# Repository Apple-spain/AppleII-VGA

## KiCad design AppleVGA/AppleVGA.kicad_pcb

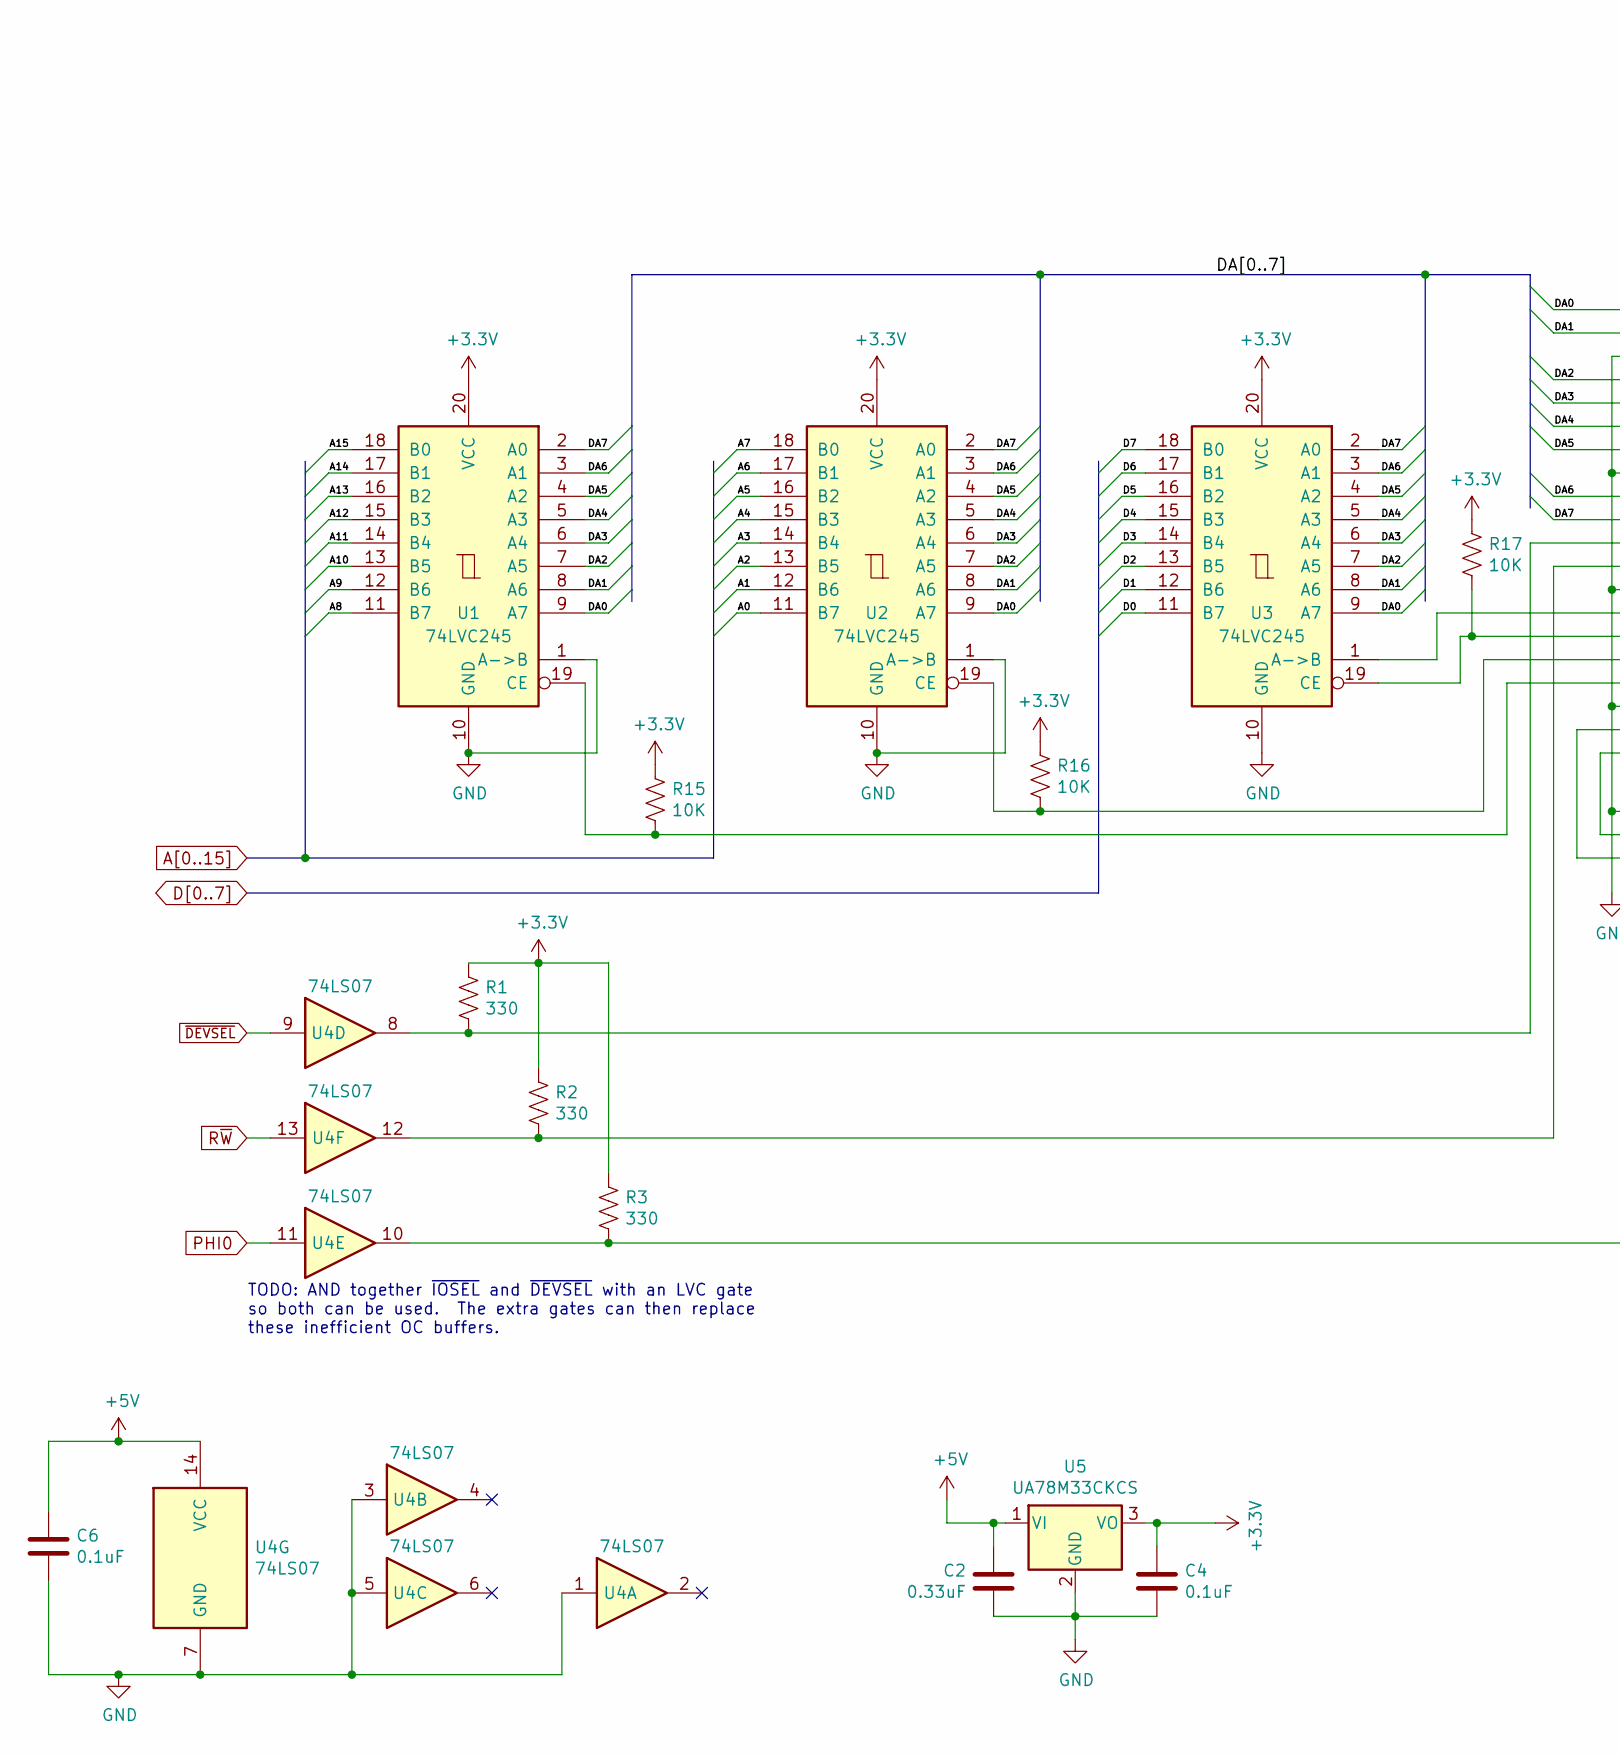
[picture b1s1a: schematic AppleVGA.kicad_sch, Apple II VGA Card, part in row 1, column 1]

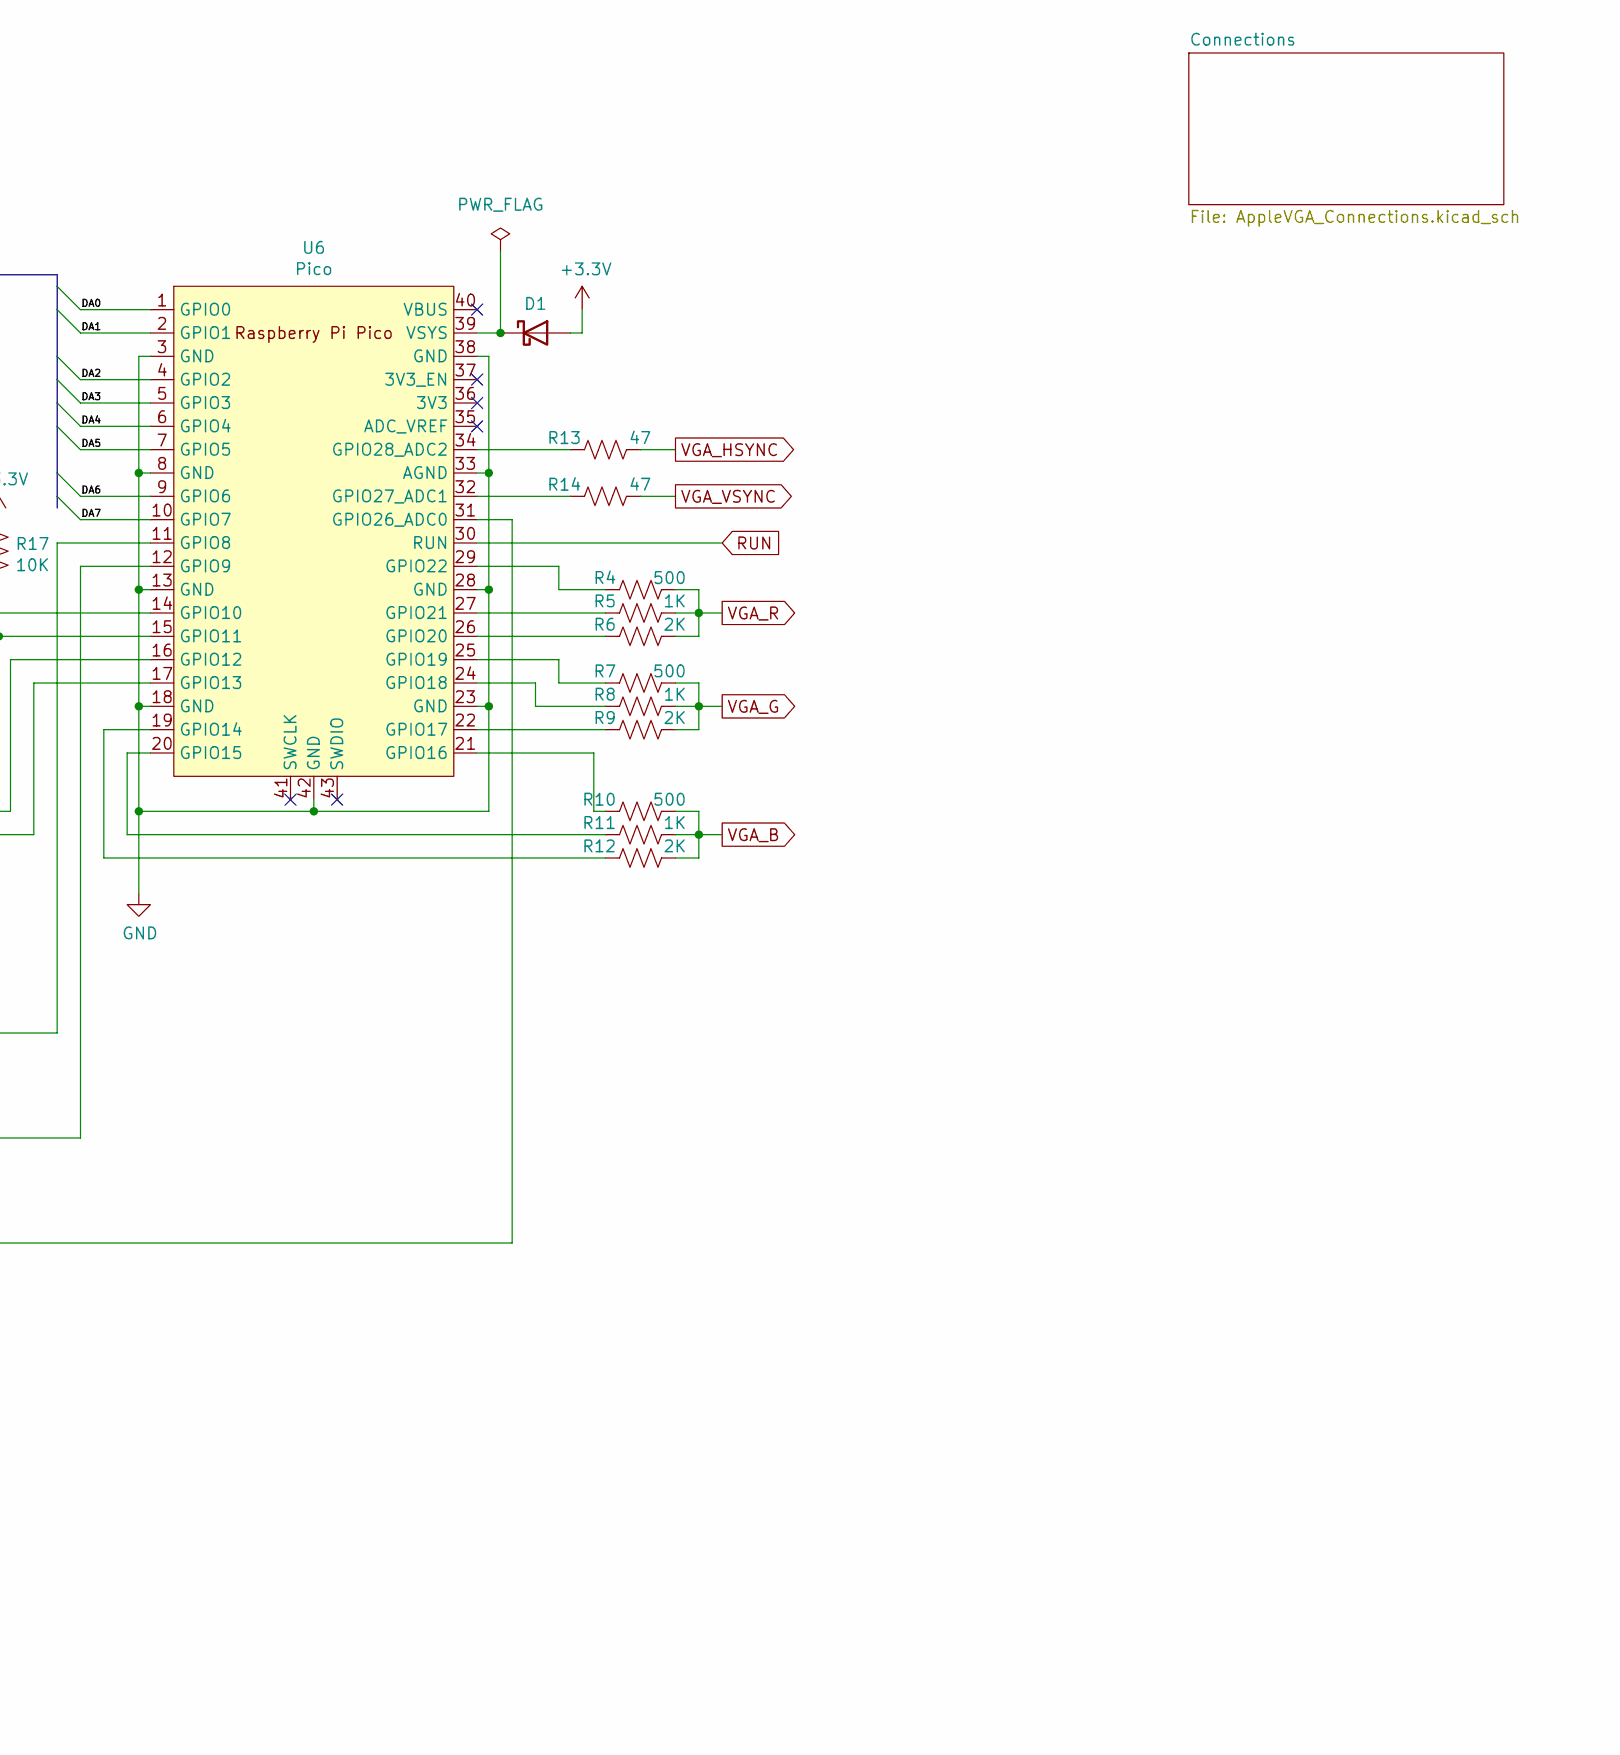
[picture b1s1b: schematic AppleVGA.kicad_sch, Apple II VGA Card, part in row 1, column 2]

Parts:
C2: 0.33uF; C_Disc_D4.3mm_W1.9mm_P5.00mm
C4, C6: 0.1uF; C_Disc_D4.3mm_W1.9mm_P5.00mm
D1: D_Schottky; D_DO-41_SOD81_P10.16mm_Horizontal
R1, R2, R3: 330; R_Axial_DIN0207_L6.3mm_D2.5mm_P10.16mm_Horizontal
R4, R7, R10: 500; R_Axial_DIN0207_L6.3mm_D2.5mm_P10.16mm_Horizontal
R5, R8, R11: 1K; R_Axial_DIN0207_L6.3mm_D2.5mm_P10.16mm_Horizontal
R6, R9, R12: 2K; R_Axial_DIN0207_L6.3mm_D2.5mm_P10.16mm_Horizontal
R13, R14: 47; R_Axial_DIN0207_L6.3mm_D2.5mm_P10.16mm_Horizontal
R15, R16, R17: 10K; R_Axial_DIN0207_L6.3mm_D2.5mm_P10.16mm_Horizontal
U1, U2, U3: 74LVC245; DIP-20_W7.62mm_Socket
U4: 74LS07; DIP-14_W7.62mm_Socket
U5: UA78M33CKCS; TO-220-3_Horizontal_TabDown
U6: Pico; RPi_Pico_SMD_TH

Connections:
+3.3V: C4.1, D1.2 (A), R1.1, R2.1, R3.1, R15.1, R16.1, R17.1, U1.20 (VCC), U2.20 (VCC), U3.20 (VCC), U5.3 (VO); also elsewhere on the board
+5V: C2.2, C6.1, U4.14 (VCC), U5.1 (VI); also elsewhere on the board
/DA0: U1.9 (A7), U2.9 (A7), U3.9 (A7), U6.1 (GPIO0)
/DA1: U1.8 (A6), U2.8 (A6), U3.8 (A6), U6.2 (GPIO1)
/DA2: U1.7 (A5), U2.7 (A5), U3.7 (A5), U6.4 (GPIO2)
/DA3: U1.6 (A4), U2.6 (A4), U3.6 (A4), U6.5 (GPIO3)
/DA4: U1.5 (A3), U2.5 (A3), U3.5 (A3), U6.6 (GPIO4)
/DA5: U1.4 (A2), U2.4 (A2), U3.4 (A2), U6.7 (GPIO5)
/DA6: U1.3 (A1), U2.3 (A1), U3.3 (A1), U6.9 (GPIO6)
/DA7: U1.2 (A0), U2.2 (A0), U3.2 (A0), U6.10 (GPIO7)
A0: U2.11 (B7); also elsewhere on the board
A1: U2.12 (B6); also elsewhere on the board
A2: U2.13 (B5); also elsewhere on the board
A3: U2.14 (B4); also elsewhere on the board
A4: U2.15 (B3); also elsewhere on the board
A5: U2.16 (B2); also elsewhere on the board
A6: U2.17 (B1); also elsewhere on the board
A7: U2.18 (B0); also elsewhere on the board
A8: U1.11 (B7); also elsewhere on the board
A9: U1.12 (B6); also elsewhere on the board
A10: U1.13 (B5); also elsewhere on the board
A11: U1.14 (B4); also elsewhere on the board
A12: U1.15 (B3); also elsewhere on the board
A13: U1.16 (B2); also elsewhere on the board
A14: U1.17 (B1); also elsewhere on the board
A15: U1.18 (B0); also elsewhere on the board
D0: U3.11 (B7); also elsewhere on the board
D1: U3.12 (B6); also elsewhere on the board
D2: U3.13 (B5); also elsewhere on the board
D3: U3.14 (B4); also elsewhere on the board
D4: U3.15 (B3); also elsewhere on the board
D5: U3.16 (B2); also elsewhere on the board
D6: U3.17 (B1); also elsewhere on the board
D7: U3.18 (B0); also elsewhere on the board
GND: C2.1, C4.2, C6.2, U1.1 (A->B), U1.10 (GND), U2.1 (A->B), U2.10 (GND), U3.10 (GND), U4.1, U4.3, U4.5, U4.7 (GND), U5.2 (GND), U6.3 (GND), U6.8 (GND), U6.13 (GND), U6.18 (GND), U6.23 (GND), U6.28 (GND), U6.33 (AGND), U6.38 (GND), U6.42 (GND); also elsewhere on the board
unnamed: D1.1 (K), U6.39 (VSYS)
unnamed: R15.2, U1.19 (CE), U6.17 (GPIO13)
unnamed: R16.2, U2.19 (CE), U6.16 (GPIO12)
unnamed: U3.1 (A->B), U6.14 (GPIO10)
unnamed: R17.2, U3.19 (CE), U6.15 (GPIO11)
unnamed: R1.2, U4.8, U6.11 (GPIO8)
unnamed: R2.2, U4.12, U6.12 (GPIO9)
unnamed: R12.1, U6.19 (GPIO14)
unnamed: R11.1, U6.20 (GPIO15)
unnamed: R10.1, U6.21 (GPIO16)
unnamed: R9.1, U6.22 (GPIO17)
unnamed: R8.1, U6.24 (GPIO18)
unnamed: R7.1, U6.25 (GPIO19)
unnamed: R6.1, U6.26 (GPIO20)
unnamed: R5.1, U6.27 (GPIO21)
unnamed: R4.1, U6.29 (GPIO22)
unnamed: R3.2, U4.10, U6.31 (GPIO26_ADC0)
unnamed: R14.1, U6.32 (GPIO27_ADC1)
unnamed: R13.1, U6.34 (GPIO28_ADC2)
PHI0: U4.11; also elsewhere on the board
RUN: U6.30 (RUN); also elsewhere on the board
R~W: U4.13; also elsewhere on the board
VGA_B: R10.2, R11.2, R12.2; also elsewhere on the board
VGA_G: R7.2, R8.2, R9.2; also elsewhere on the board
VGA_HSYNC: R13.2; also elsewhere on the board
VGA_R: R4.2, R5.2, R6.2; also elsewhere on the board
VGA_VSYNC: R14.2; also elsewhere on the board
~DEVSEL: U4.9; also elsewhere on the board

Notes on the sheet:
TODO: AND together ~{IOSEL} and ~{DEVSEL} with an LVC gate so both can be used. The extra gates can then replace these inefficient OC buffers.

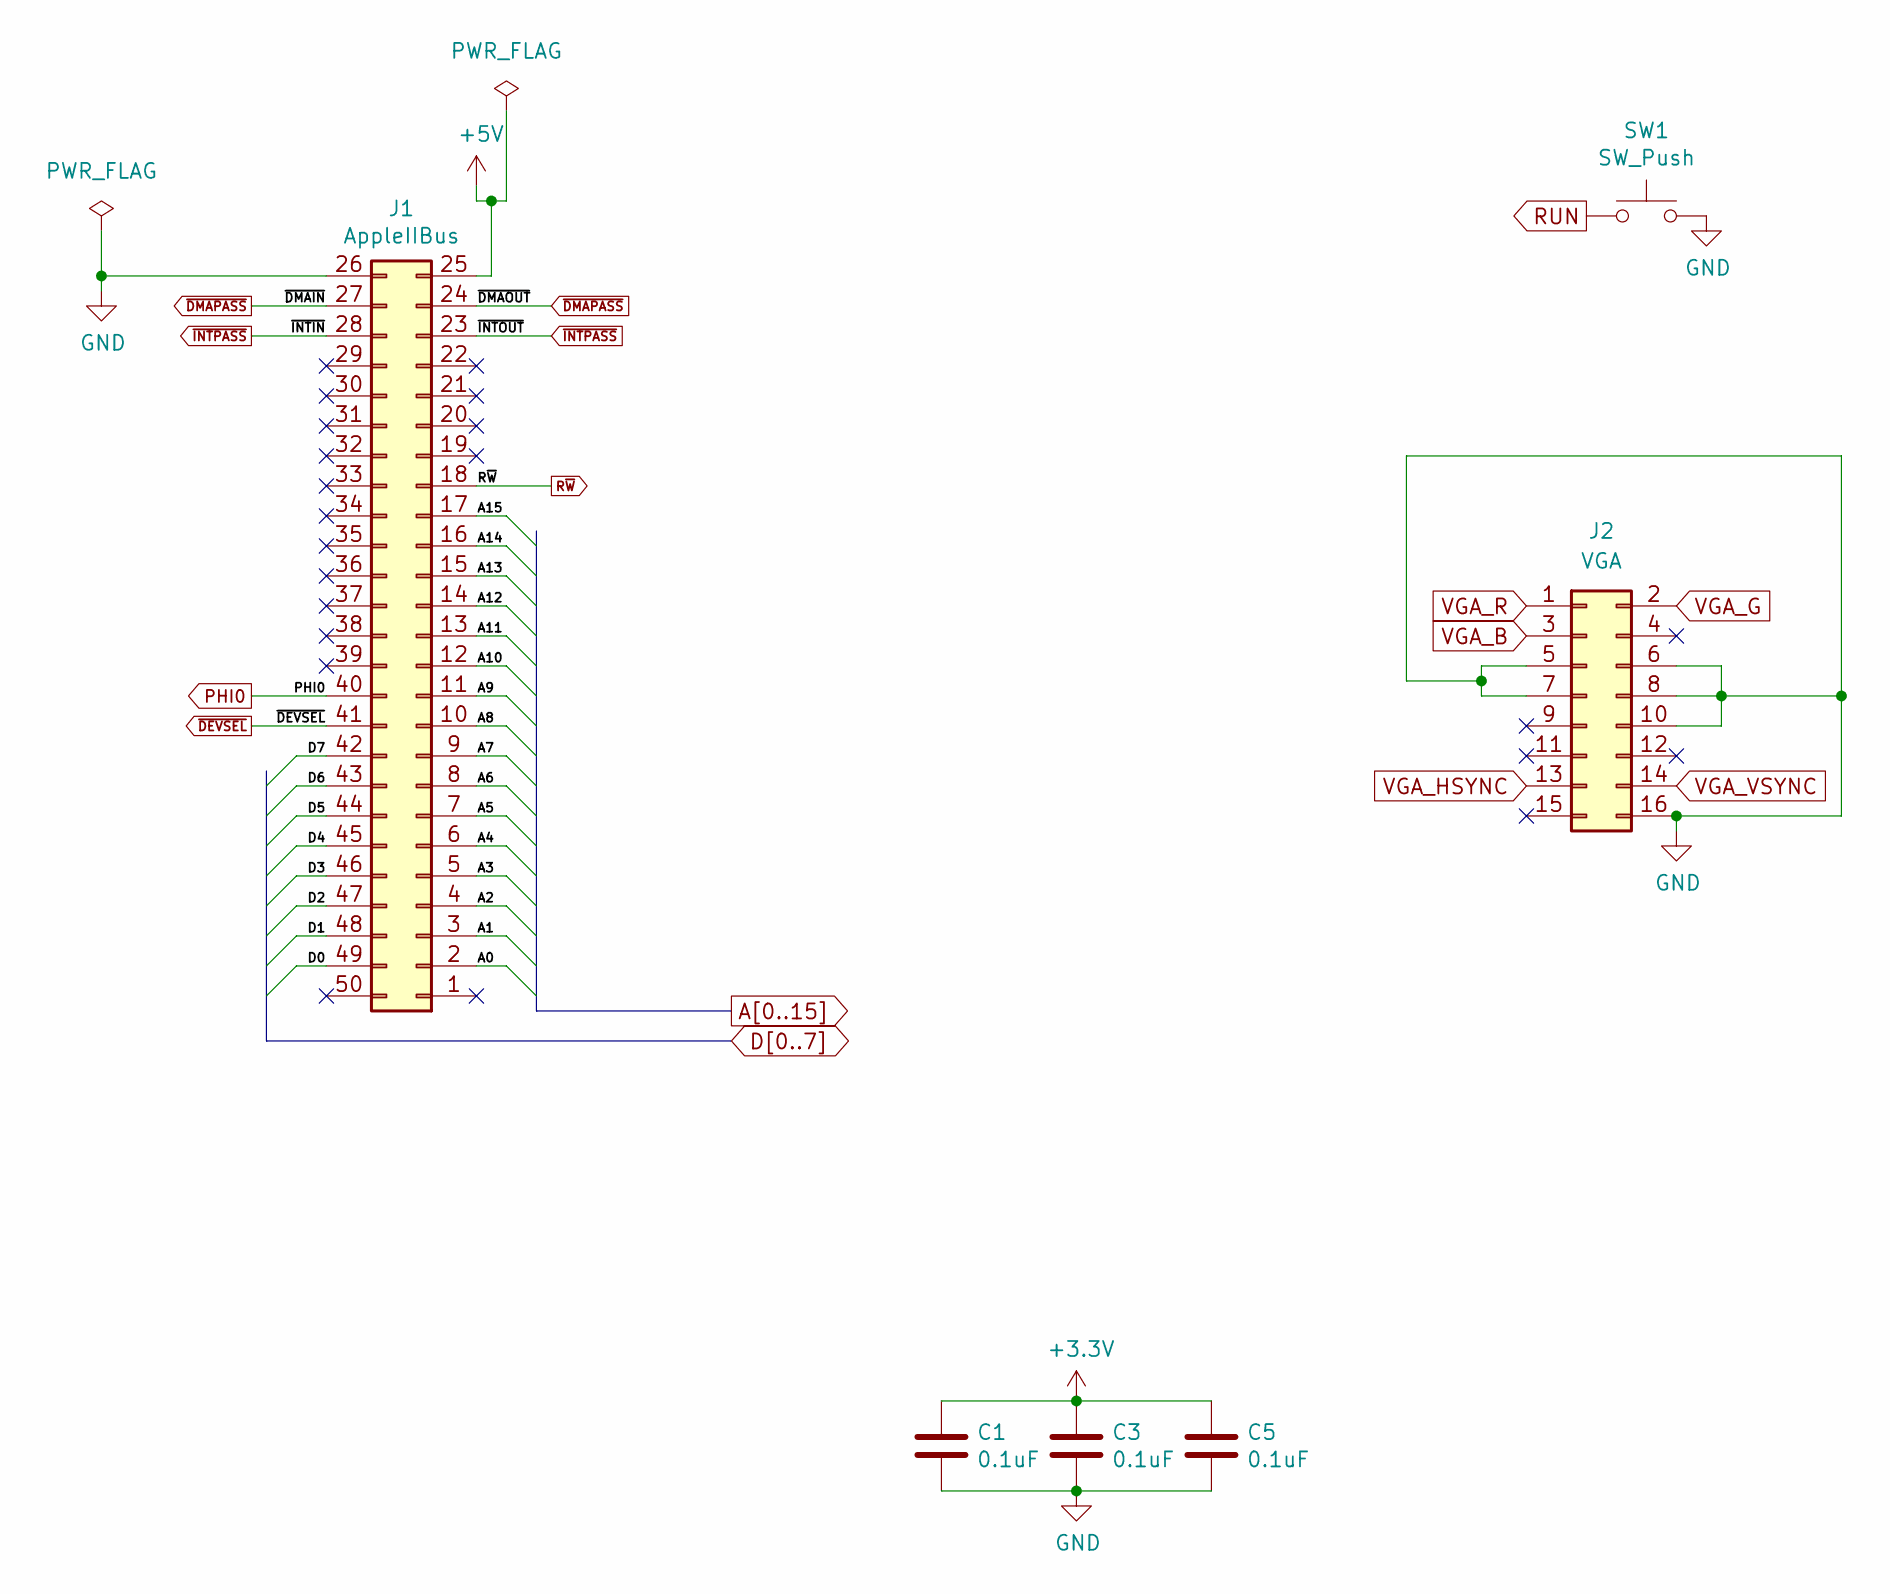
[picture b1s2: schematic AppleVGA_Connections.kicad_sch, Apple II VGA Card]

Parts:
C1, C3, C5: 0.1uF; C_Disc_D4.3mm_W1.9mm_P5.00mm
J1: AppleIIBus; AppleIIBus_Edge
J2: VGA; PinSocket_2x08_P2.54mm_Vertical
SW1: SW_Push; SW_PUSH_6mm_H5mm

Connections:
+3.3V: C1.1, C3.1, C5.1; also elsewhere on the board
+5V: J1.25; also elsewhere on the board
A0: J1.2; also elsewhere on the board
A1: J1.3; also elsewhere on the board
A2: J1.4; also elsewhere on the board
A3: J1.5; also elsewhere on the board
A4: J1.6; also elsewhere on the board
A5: J1.7; also elsewhere on the board
A6: J1.8; also elsewhere on the board
A7: J1.9; also elsewhere on the board
A8: J1.10; also elsewhere on the board
A9: J1.11; also elsewhere on the board
A10: J1.12; also elsewhere on the board
A11: J1.13; also elsewhere on the board
A12: J1.14; also elsewhere on the board
A13: J1.15; also elsewhere on the board
A14: J1.16; also elsewhere on the board
A15: J1.17; also elsewhere on the board
D0: J1.49; also elsewhere on the board
D1: J1.48; also elsewhere on the board
D2: J1.47; also elsewhere on the board
D3: J1.46; also elsewhere on the board
D4: J1.45; also elsewhere on the board
D5: J1.44; also elsewhere on the board
D6: J1.43; also elsewhere on the board
D7: J1.42; also elsewhere on the board
GND: C1.2, C3.2, C5.2, J1.26, J2.5, J2.6, J2.7, J2.8, J2.10, J2.16, SW1.2; also elsewhere on the board
PHI0: J1.40; also elsewhere on the board
RUN: SW1.1; also elsewhere on the board
R~W: J1.18; also elsewhere on the board
VGA_B: J2.3; also elsewhere on the board
VGA_G: J2.2; also elsewhere on the board
VGA_HSYNC: J2.13; also elsewhere on the board
VGA_R: J2.1; also elsewhere on the board
VGA_VSYNC: J2.14; also elsewhere on the board
~DEVSEL: J1.41; also elsewhere on the board
~DMAPASS: J1.24, J1.27
~INTPASS: J1.23, J1.28

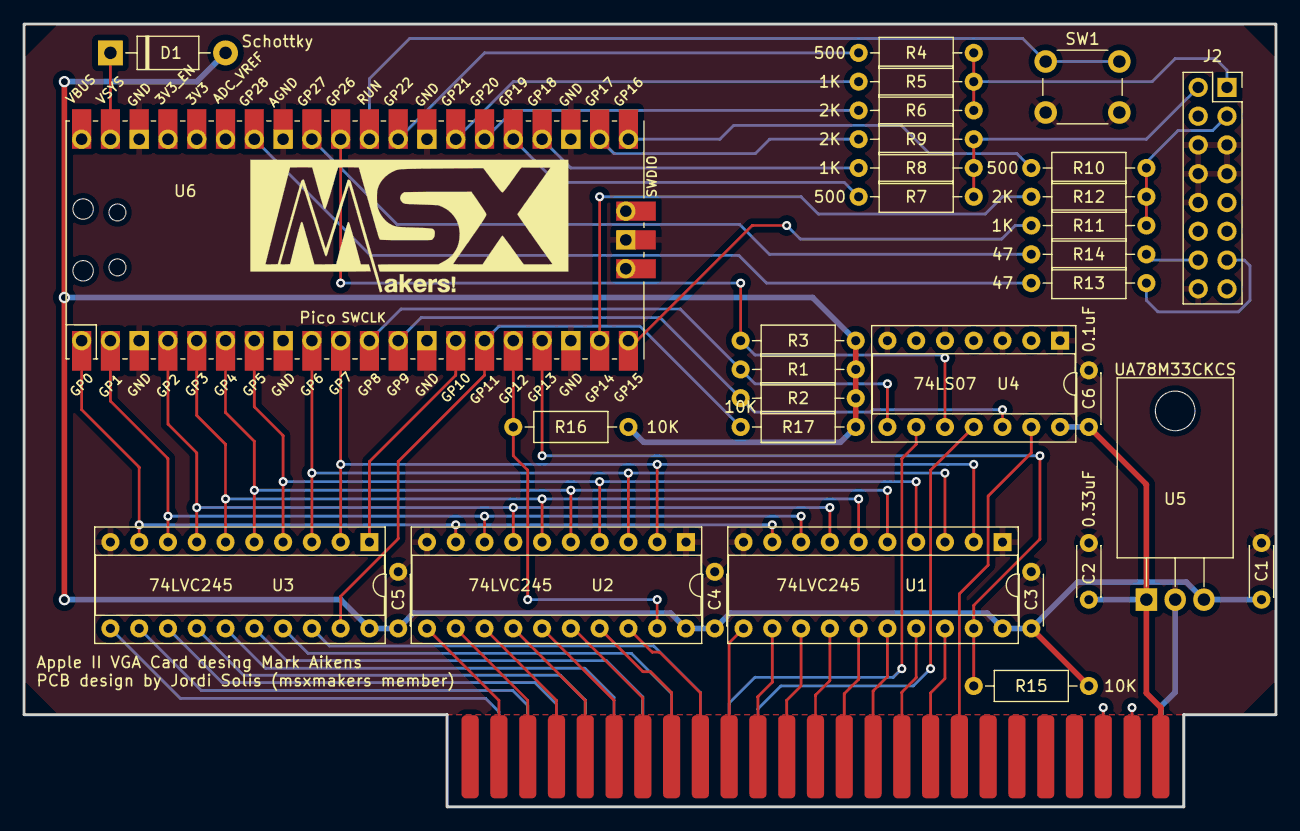
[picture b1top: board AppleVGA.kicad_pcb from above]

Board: 2 copper layers, 110.5 x 69.1 mm, 33 parts (0 on the bottom side), 65 nets.

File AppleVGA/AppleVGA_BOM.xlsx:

referencia | Descripcion | qty | P_Ali
PCB | Apple2vga | 1 | https://github.com/markadev/AppleII-VGA/
C1 – C58 | 0.1 uF, MLCC, 5 mm Pitch | 5 | https://es.aliexpress.com/item/1005001715033995.html?gateway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
C2 | Condensador 330nF THT radial 5.00mm entre pines | 1 | https://es.aliexpress.com/item/1005001715033995.html?gateway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
D1 | Diodo axial THT DO-41 schottky | 1 | https://es.aliexpress.com/item/1005004443278541.html?spm=a2g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
J2 | Conector PinHeader 1x08 paso 2.54mm Vertical | 1 | https://es.aliexpress.com/item/4000857385112.html?spm=a2g0o.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
J3 | Conector DSUB-15-HD VGA Female Horizontal (90º) | 1 | https://es.aliexpress.com/item/1005004701670869.html?spm=a2g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
R1-R3 | Resistencia 330R Axial THT 1/4W | 3 | https://es.aliexpress.com/item/4000695402017.html?spm=a2g0s.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
R4, R7, R10 | Resistencia 500R Axial THT 1/4W (510R) | 3 | https://es.aliexpress.com/item/4000695402017.html?spm=a2g0s.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
R5, R8, R11 | Resistencia 1K Axial THT 1/4W | 3 | https://es.aliexpress.com/item/4000695402017.html?spm=a2g0s.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
R6, R9, R12 | Resistencia 2K Axial THT 1/4W | 3 | https://es.aliexpress.com/item/4000695402017.html?spm=a2g0s.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
R13, R14 | Resistencia 47R Axial THT 1/4W | 2 | https://es.aliexpress.com/item/4000695402017.html?spm=a2g0s.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
R15-R17 | Resistencia 10K Axial THT 1/4W | 3 | https://es.aliexpress.com/item/4000695402017.html?spm=a2g0s.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
SW1 | Botón pulsador DPST (on)-off paso 6mm | 1 | https://es.aliexpress.com/item/4000695402017.html?spm=a2g0s.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
U1-U3 | 74LVC245 DIP-20 | 3 | https://es.aliexpress.com/item/1005003499320188.html?spm=a2g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
U4 | 74LS07 DIP-14 | 1 | https://es.aliexpress.com/item/1005003087978058.html?spm=a2g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
U5 | Regulador de voltaje 3.3v UA78M33CKCS TO-220-3 | 1 | https://es.aliexpress.com/item/32826540392.html?spm=a2g0o.or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
U6 | MCU RaspberryPi Pico | 1 | https://es.aliexpress.com/item/1005005658292169.html?spm=a2g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
Z1-Z3 | zocalos 20DIP300 | 3 | https://es.aliexpress.com/item/4001048163251.html?spm=a2g0o.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
Z4 | zocalos 14DIP300 | 1 | https://es.aliexpress.com/item/4001048163251.html?spm=a2g0o.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
no_ref | adaptador vga | 1 | https://es.aliexpress.com/item/1005004328077008.html?spm=a2g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

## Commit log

2023-12-15 Fichero compilado

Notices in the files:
AppleVGA/AppleVGA.kicad_pcb:
Licensed under CERN-OHL-P V2.0 (https://ohwr.org/cern_ohl_p_v2.txt)
Copyright (c) 2021-2022 Mark Aikens
